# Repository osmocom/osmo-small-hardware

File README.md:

osmo-small-hardware - Various small Osmocom Hardware Projects
=============================================================

This repository contains a number of OSHW (open source hardware)
designs.  They are part of the [Osmocom](https://osmocom.org/) Open
Source Mobile Communications project.

Most of the designs are done in EAGLE CAD; the schematics and board
design files as well as the BOM are contained in this repository.

GIT Repository
--------------

You can clone from the official osmo-small-hardware repository using

	git clone https://gitea.osmocom.org/electronics/osmo-small-hardware

There is a web interface at <https://gitea.osmocom.org/electronics/osmo-small-hardware>

Contributing
------------

Our coding standards are described at
https://osmocom.org/projects/cellular-infrastructure/wiki/Coding_standards

We us a gerrit based patch submission/review process for managing
contributions.  Please see
https://osmocom.org/projects/cellular-infrastructure/wiki/Gerrit for
more details

clock-converter
---------------

The osmo-clock-conv is a small board for low-jitter conversion of a sine
clock into a square clock, based around the LTC6957-4.

* [Homapege](https://osmocom.org/projects/osmo-clock-conv)

clock-generator
---------------

Osmocom Clock Generator board, using the Si5351C clock synthesizer to
derive up to 8 different clocks from a single clock reference, such as a
10MHz GPS-DO or OCXO.

* [Homepage](https://osmocom.org/projects/osmo-clock-gen)

dus-lmt-breakout
----------------

This is a break-out board for the LMT port of Ericsson DUS-31/41
baseband units.

e1-tap
------

The Osmocom E1/T1 tap adapter allows you to tap into the communication
of an E1/T1 line.

* [Homepage](https://osmocom.org/projects/e1-tap)

eksos-rj45-breakout
-------------------

This contains a couple of break-out boards which can be used to break out the
ISDN / PSTN ports of a Nokia EKSOS V5 access network.

gtm900-breakout
---------------

Break-out board for the GTM900B Calypso based GSM cellular modem.

mpcie-breakout
--------------

This is a small break-out board for miniPCIe (mPCIe) type cellular /
WWAN modems.

* [Homepage](https://osmocom.org/projects/mpcie-breakout)

multivoltage-uart
-----------------

* [Homepage](https://osmocom.org/projects/mv-uart)

ngff-breakout
-------------

This is a small break-out board for M.2 (NGFF) type cellular / WWAN
modems.

* [Homepage](https://osmocom.org/projects/ngff-breakout)

ohm4-ocxo
---------

osmo-lea6t-gps
--------------

Small evaluation board for the u-blox LEA6-T timing GPS receiver.

osmo-nvs-gps
------------

Small evaluation board for the NVS GPS receiver.

rj45-jumper-box
---------------

A jumper box for RJ45 cables. Useful for the many different RS232
console pin-outs on RJ45.

* [Homepage](https://osmocom.org/projects/misc-hardware/wiki/RJ45_jumper_box)

rj45-switch
-----------

sc14dect-breakout
-----------------

Small evaluation board for the SC15 DECT module

sfp-breakout + sfp-experimenter
-------------------------------

Boards for playing with SFP transceivers

* [Homepage](https://osmocom.org/projects/misc-hardware/wiki/Sfp-breakout)

siu-clock-breakout
------------------

A break-out board for the clock/sync port on the Ericsson SIU-02

rbs6k-diy-rack
--------------

A DYI small rack for housing Ericsson RBS 6000 equipment like DUL + DUG + RUS made from wooden panels and a laser-cut back plate for fans.

fcd155-breakout
---------------

This is a small break-out board to adapt the RAD FCD-155 8xE1 high-density 44-pin D-SUB connector to 8xRJ45 in standard E1 pinout.

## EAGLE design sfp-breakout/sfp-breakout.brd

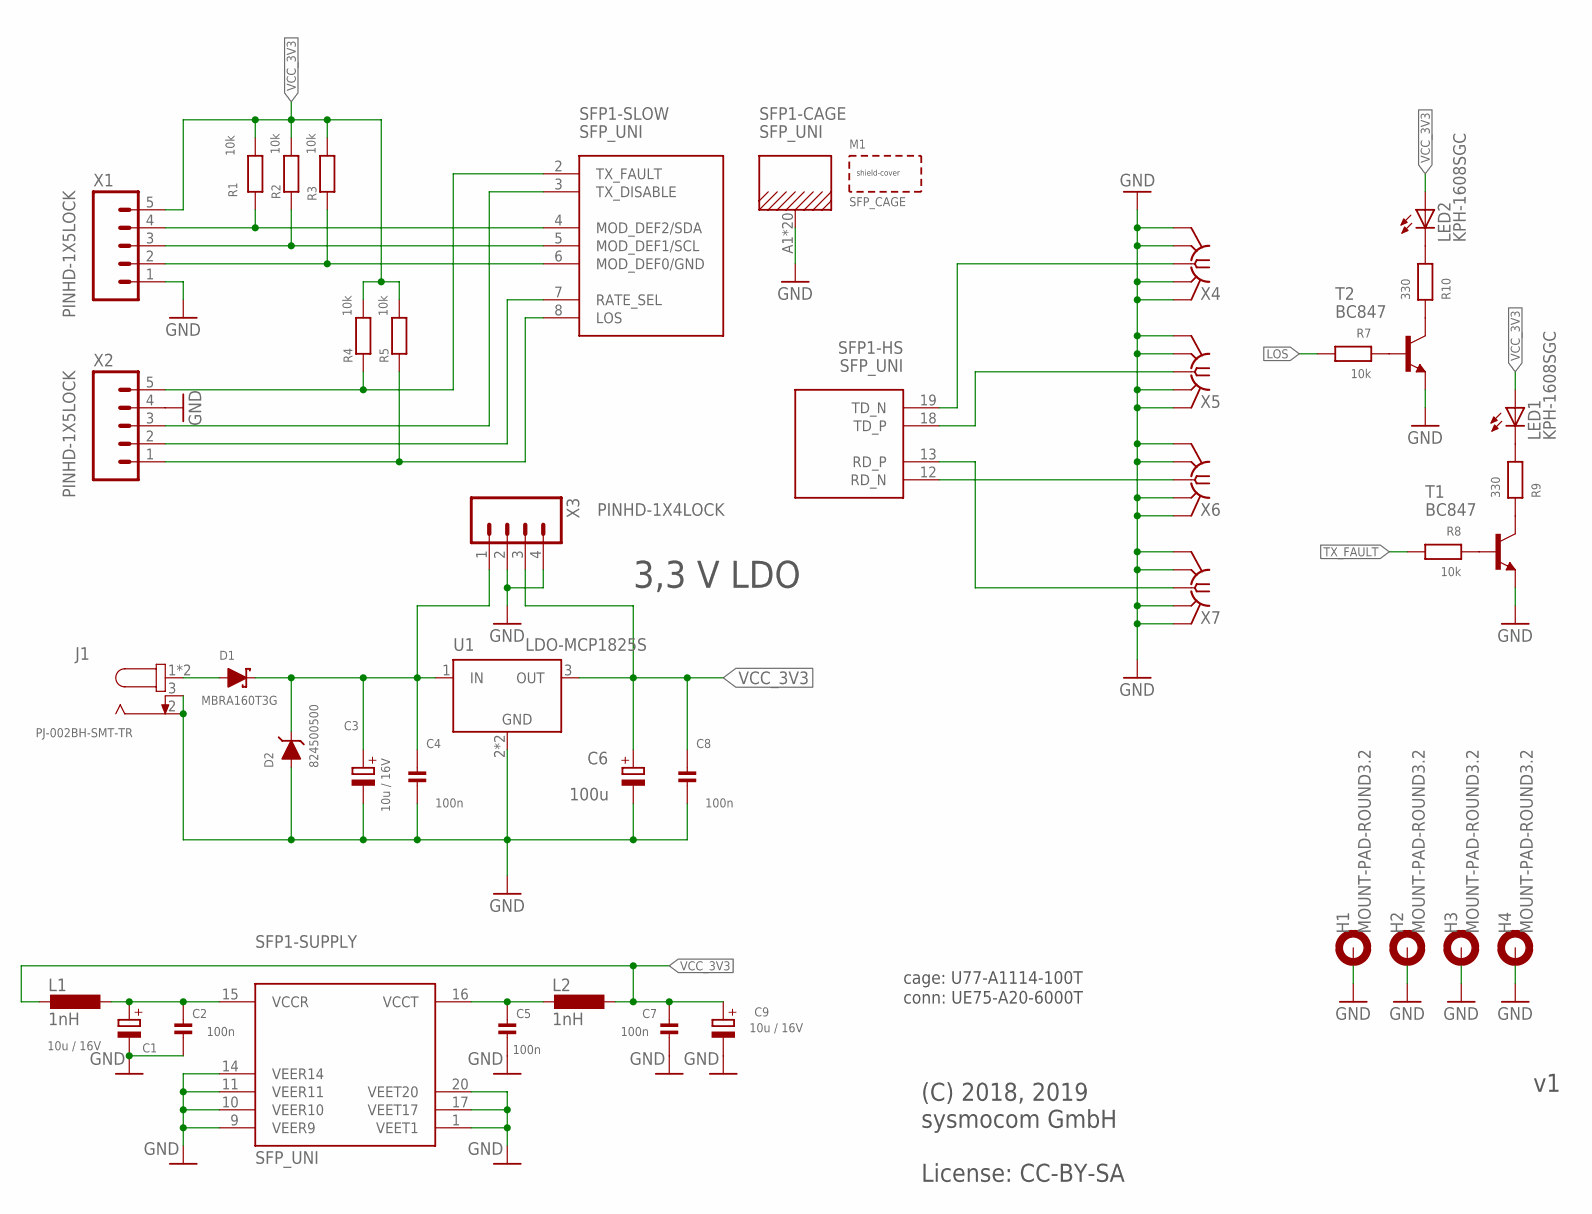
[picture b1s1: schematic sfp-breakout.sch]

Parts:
C1, C3, C9: 10u / 16V; CPOL1206; MANUFACTURERPARTNUMBER CL31A106KOHNNNE
C2, C4, C5, C7, C8: 100n; _0603; MANUFACTURERPARTNUMBER CL10B104KO8NNNC
C6: 100u; CT6032; MANUFACTURERPARTNUMBER TPSC107K006R0150
D1: MBRA160T3G; SMADIODE; MANUFACTURERPARTNUMBER B260A-13-F
D2: 824500500; SMADIODE; MANUFACTURERPARTNUMBER 824500500
H1, H2, H3, H4: MOUNT-PAD-ROUND3.2; 3,2-PAD; MANUFACTURERPARTNUMBER UNKNOWN MANUFACTURER PART NUMBER
J1: PJ-002BH-SMT-TR; 694108106102; MANUFACTURERPARTNUMBER PJ-002BH-SMT-TR
L1, L2: 1nH; 0603; MANUFACTURERPARTNUMBER AIMC-0603-1N0S-T
LED1, LED2: KPH-1608SGC; CHIP-LED0603; MANUFACTURERPARTNUMBER UNKNOWN MANUFACTURER PART NUMBER
R1, R2, R3, R4, R5, R7, R8: 10k; _0603; MANUFACTURERPARTNUMBER RMCF0603FT10K0
R9, R10: 330; _0603; MANUFACTURERPARTNUMBER RC0603FR-07330RL
SFP1: SFP_UNI; SFP_COMBINED; MANUFACTURERPARTNUMBER UE75-A20-6000T
T1, T2: BC847; SOT23-BEC; MANUFACTURERPARTNUMBER BC847C,215
U1: LDO-MCP1825S; SOT223; MANUFACTURERPARTNUMBER MCP1825ST-3302E/DB
X1, X2: PINHD-1X5LOCK; 1X05_LOCK; MANUFACTURERPARTNUMBER UNKNOWN MANUFACTURER PART NUMBER
X3: PINHD-1X4LOCK; 1X04_LOCK; MANUFACTURERPARTNUMBER UNKNOWN MANUFACTURER PART NUMBER
X4, X5, X6, X7: SMA-F-S-EDGE; MANUFACTURERPARTNUMBER UNKNOWN MANUFACTURER PART NUMBER

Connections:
+VIN: C3.+, C4.1, D1.C, D2.C, U1.1 (IN), X3.1
GND: C1.-, C2.2, C3.-, C4.2, C5.2, C6.-, C7.2, C8.2, C9.-, D2.A, H1.B3,2, H2.B3,2, H3.B3,2, H4.B3,2, J1.2, J1.3, SFP1.1 (VEET1), SFP1.9 (VEER9), SFP1.10 (VEER10), SFP1.11 (VEER11), SFP1.14 (VEER14), SFP1.17 (VEET17), SFP1.20 (VEET20), SFP1.A1 (CAGE), SFP1.A2 (CAGE), SFP1.A3 (CAGE), SFP1.A4 (CAGE), SFP1.A5 (CAGE), SFP1.A6 (CAGE), SFP1.A7 (CAGE), SFP1.A8 (CAGE), SFP1.A10 (CAGE), SFP1.A11 (CAGE), SFP1.A12 (CAGE), SFP1.B1 (CAGE), SFP1.B2 (CAGE), SFP1.B3 (CAGE), SFP1.B4 (CAGE), SFP1.B5 (CAGE), SFP1.B6 (CAGE), SFP1.B7 (CAGE), SFP1.B8 (CAGE), SFP1.B10 (CAGE), T1.E, T2.E, U1.2 (GND), U1.4 (GND), X1.1, X2.4, X3.2, X3.4, X4.BG1 (GND), X4.BG2 (GND), X4.TG1 (GND), X4.TG2 (GND), X5.BG1 (GND), X5.BG2 (GND), X5.TG1 (GND), X5.TG2 (GND), X6.BG1 (GND), X6.BG2 (GND), X6.TG1 (GND), X6.TG2 (GND), X7.BG1 (GND), X7.BG2 (GND), X7.TG1 (GND), X7.TG2 (GND)
LOS: R5.1, R7.2, SFP1.8 (LOS), X2.1
MOD_DEF0/GND: R3.1, SFP1.6 (MOD_DEF0/GND), X1.2
MOD_DEF1/SCL: R2.1, SFP1.5 (MOD_DEF1/SCL), X1.3
MOD_DEF2/SDA: R1.1, SFP1.4 (MOD_DEF2/SDA), X1.4
unnamed: D1.A, J1.1, J1.1-1 (1)
unnamed: R7.1, T2.B
unnamed: LED2.C, R10.2
unnamed: C5.1, L2.2, SFP1.16 (VCCT)
unnamed: C1.+, C2.1, L1.1, SFP1.15 (VCCR)
unnamed: R10.1, T2.C
unnamed: R8.1, T1.B
unnamed: LED1.C, R9.2
unnamed: R9.1, T1.C
RATE_SEL: SFP1.7 (RATE_SEL), X2.2
RD_N: SFP1.12 (RD_N), X6.C (1)
RD_P: SFP1.13 (RD_P), X7.C (1)
TD_N: SFP1.19 (TD_N), X4.C (1)
TD_P: SFP1.18 (TD_P), X5.C (1)
TX_DISABLE: SFP1.3 (TX_DISABLE), X2.3
TX_FAULT: R4.1, R8.2, SFP1.2 (TX_FAULT), X2.5
VCC_3V3: C6.+, C7.1, C8.1, C9.+, L1.2, L2.1, LED1.A, LED2.A, R1.2, R2.2, R3.2, R4.2, R5.2, U1.3 (OUT), X1.5, X3.3

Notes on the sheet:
3,3 V LDO
(C) 2018, 2019 sysmocom GmbH License: CC-BY-SA
cage: U77-A1114-100T
conn: UE75-A20-6000T

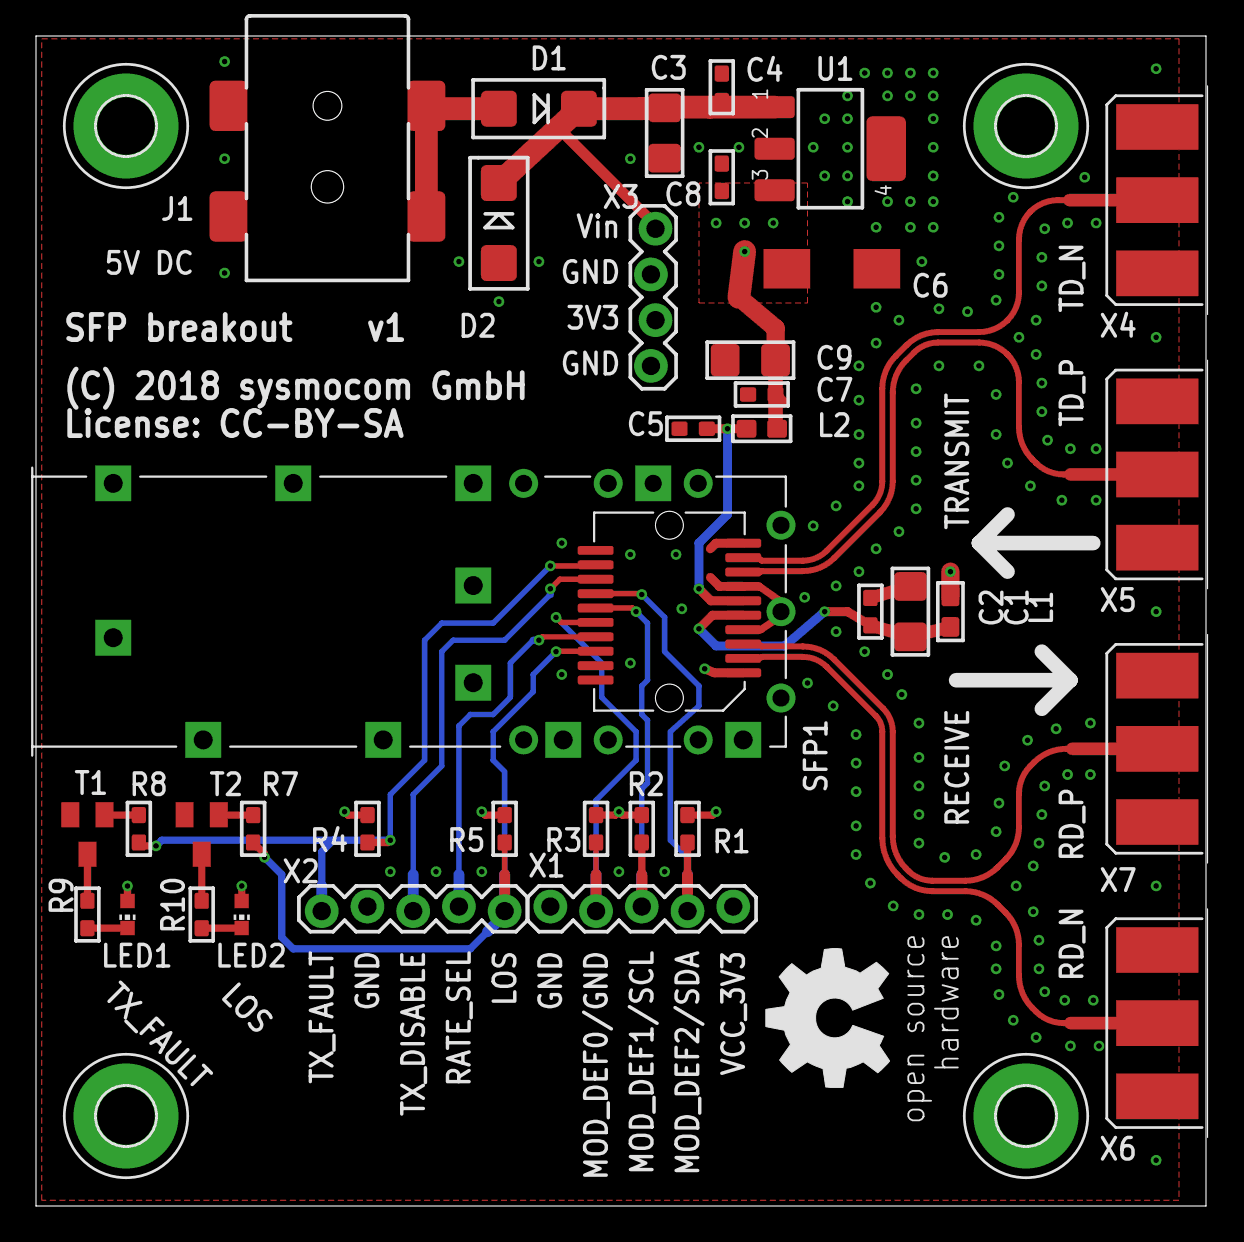
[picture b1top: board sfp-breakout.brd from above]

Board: 4 copper layers, 65.0 x 65.0 mm, 41 parts (0 on the bottom side), 23 nets.

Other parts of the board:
U$1: OSHW_8MM

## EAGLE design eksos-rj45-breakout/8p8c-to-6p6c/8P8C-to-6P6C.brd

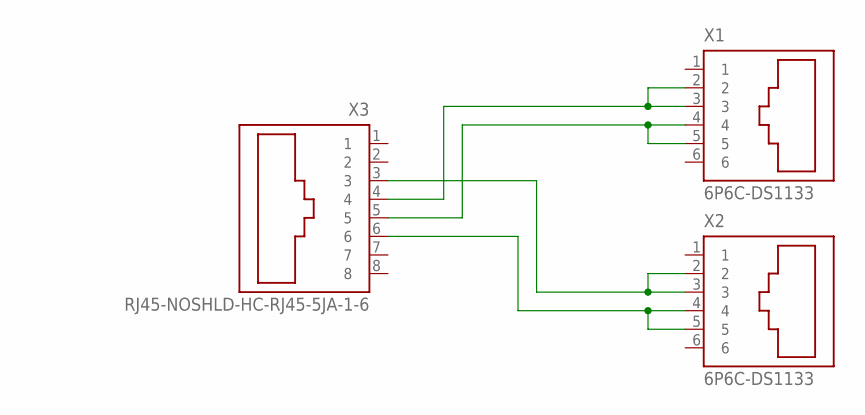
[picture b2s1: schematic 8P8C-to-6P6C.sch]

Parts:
X1, X2: 6P6C-DS1133; DS1133
X3: RJ45-NOSHLD-HC-RJ45-5JA-1-6; HC-RJ45-5JA-1-6

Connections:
unnamed: X1.2, X1.3, X3.4
unnamed: X1.4, X1.5, X3.5
unnamed: X2.2, X2.3, X3.3
unnamed: X2.4, X2.5, X3.6

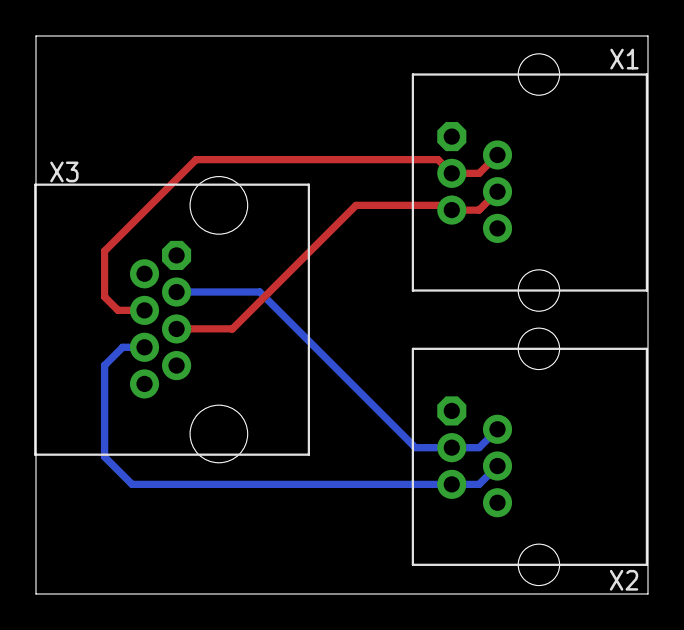
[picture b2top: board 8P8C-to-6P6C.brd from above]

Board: 2 copper layers, 34.0 x 31.0 mm, 3 parts (0 on the bottom side), 4 nets.

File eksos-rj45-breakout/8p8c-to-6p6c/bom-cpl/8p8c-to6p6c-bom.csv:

Comment,Designator,Footprint,JLCPCB Part #
6P6C,"X1, X2",DS1133,C77859
RJ45,"X3",HC-RJ45-5JA-1-6,C3000176

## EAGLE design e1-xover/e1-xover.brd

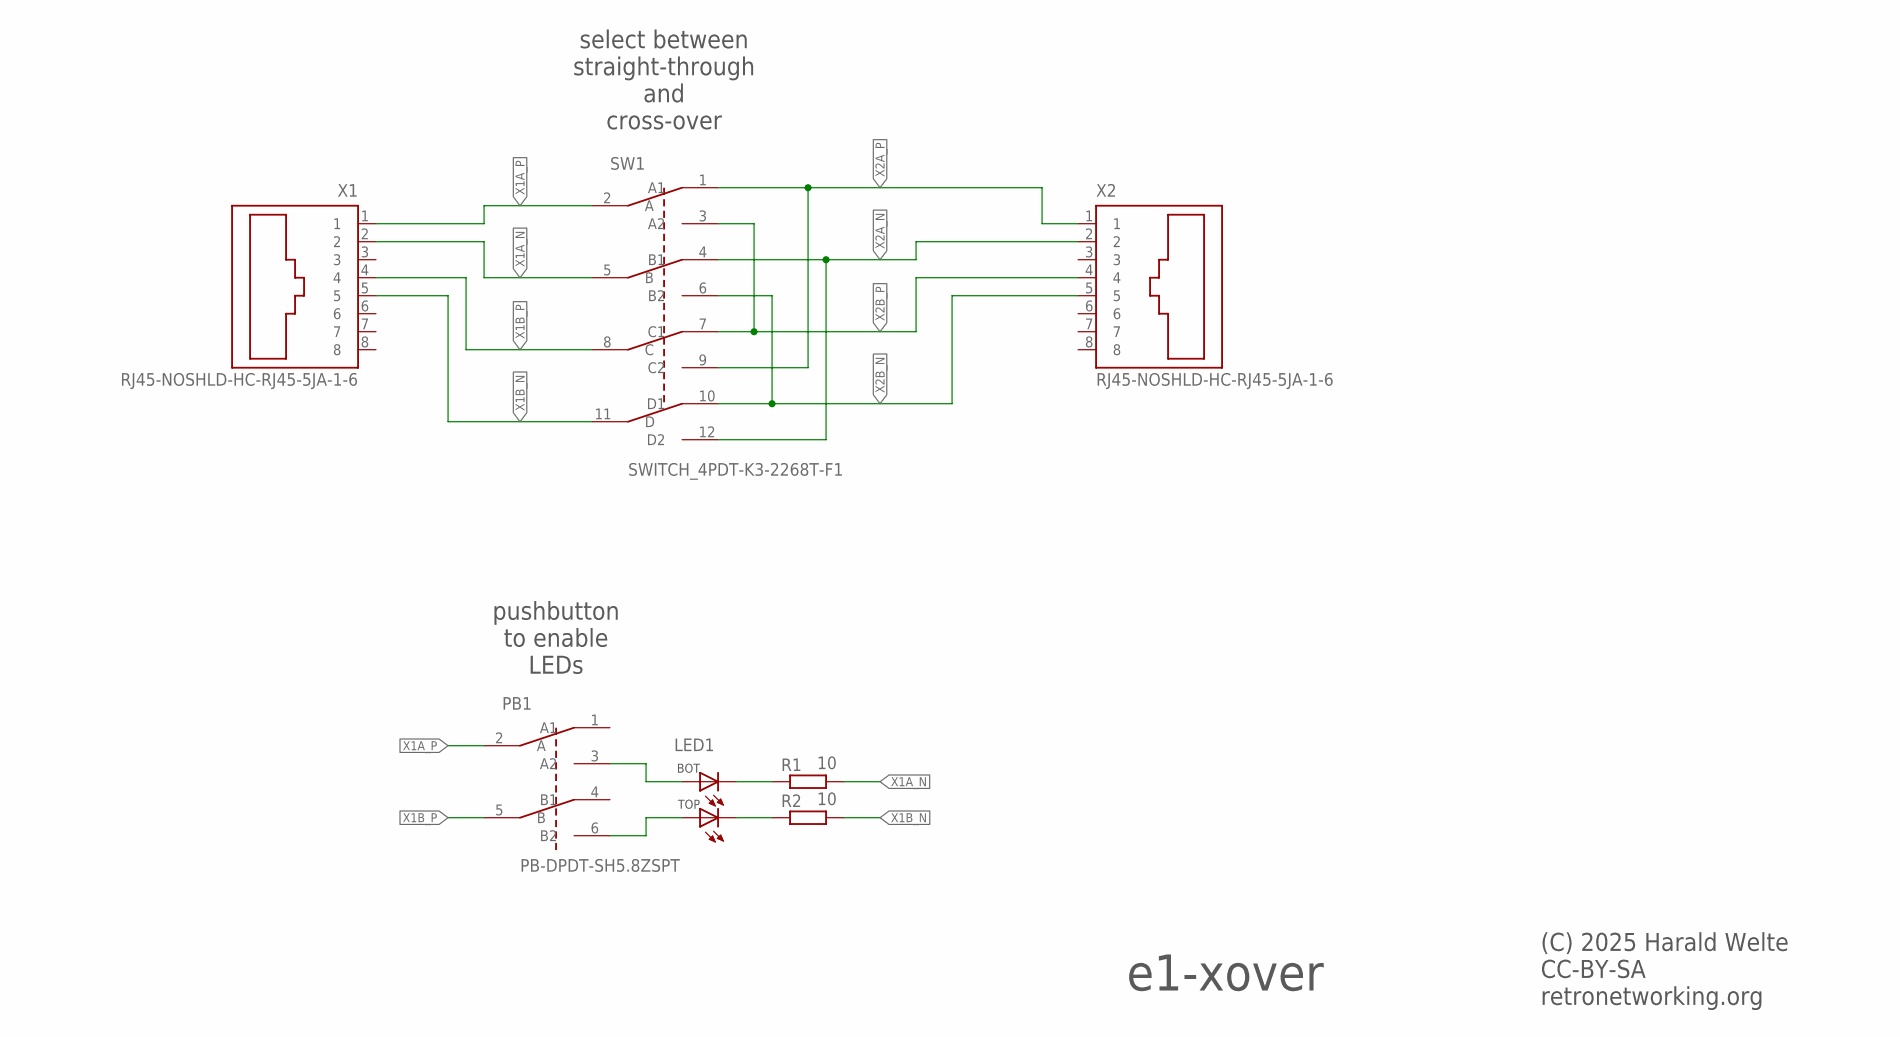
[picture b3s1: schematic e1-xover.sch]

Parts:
LED1: DIALIGHT_2V-MHK2512RGTD; MHK2512RGTD
PB1: PB-DPDT-SH5.8ZSPT; SH-5.8ZSPT
R1, R2: 10; 0207/7
SW1: SWITCH_4PDT-K3-2268T-F1; K3--2268T-F1
X1, X2: RJ45-NOSHLD-HC-RJ45-5JA-1-6; HC-RJ45-5JA-1-6

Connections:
unnamed: LED1.BK (CB), R1.1
unnamed: LED1.AK (CT), R2.1
unnamed: LED1.BA (AB), PB1.3 (A2)
unnamed: LED1.AA (AT), PB1.6 (B2)
X1A_N: R1.2, SW1.5 (B), X1.2
X1A_P: PB1.2 (A), SW1.2 (A), X1.1
X1B_N: R2.2, SW1.11 (D), X1.5
X1B_P: PB1.5 (B), SW1.8 (C), X1.4
X2A_N: SW1.4 (B1), SW1.12 (D2), X2.2
X2A_P: SW1.1 (A1), SW1.9 (C2), X2.1
X2B_N: SW1.6 (B2), SW1.10 (D1), X2.5
X2B_P: SW1.3 (A2), SW1.7 (C1), X2.4

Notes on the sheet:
e1-xover
(C) 2025 Harald Welte CC-BY-SA retronetworking.org
select between straight-through and cross-over
pushbutton to enable LEDs

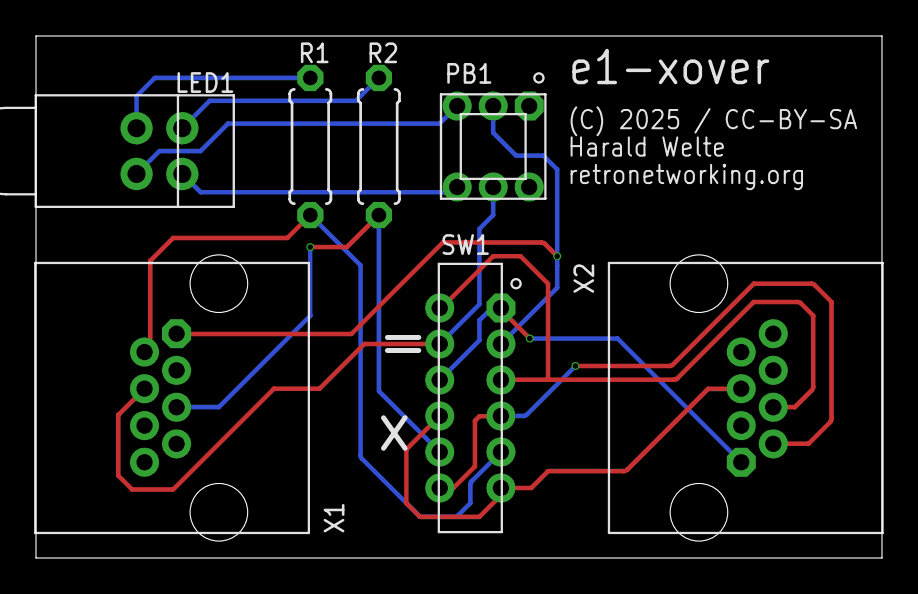
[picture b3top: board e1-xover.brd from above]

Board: 2 copper layers, 47.0 x 29.0 mm, 7 parts (0 on the bottom side), 12 nets.

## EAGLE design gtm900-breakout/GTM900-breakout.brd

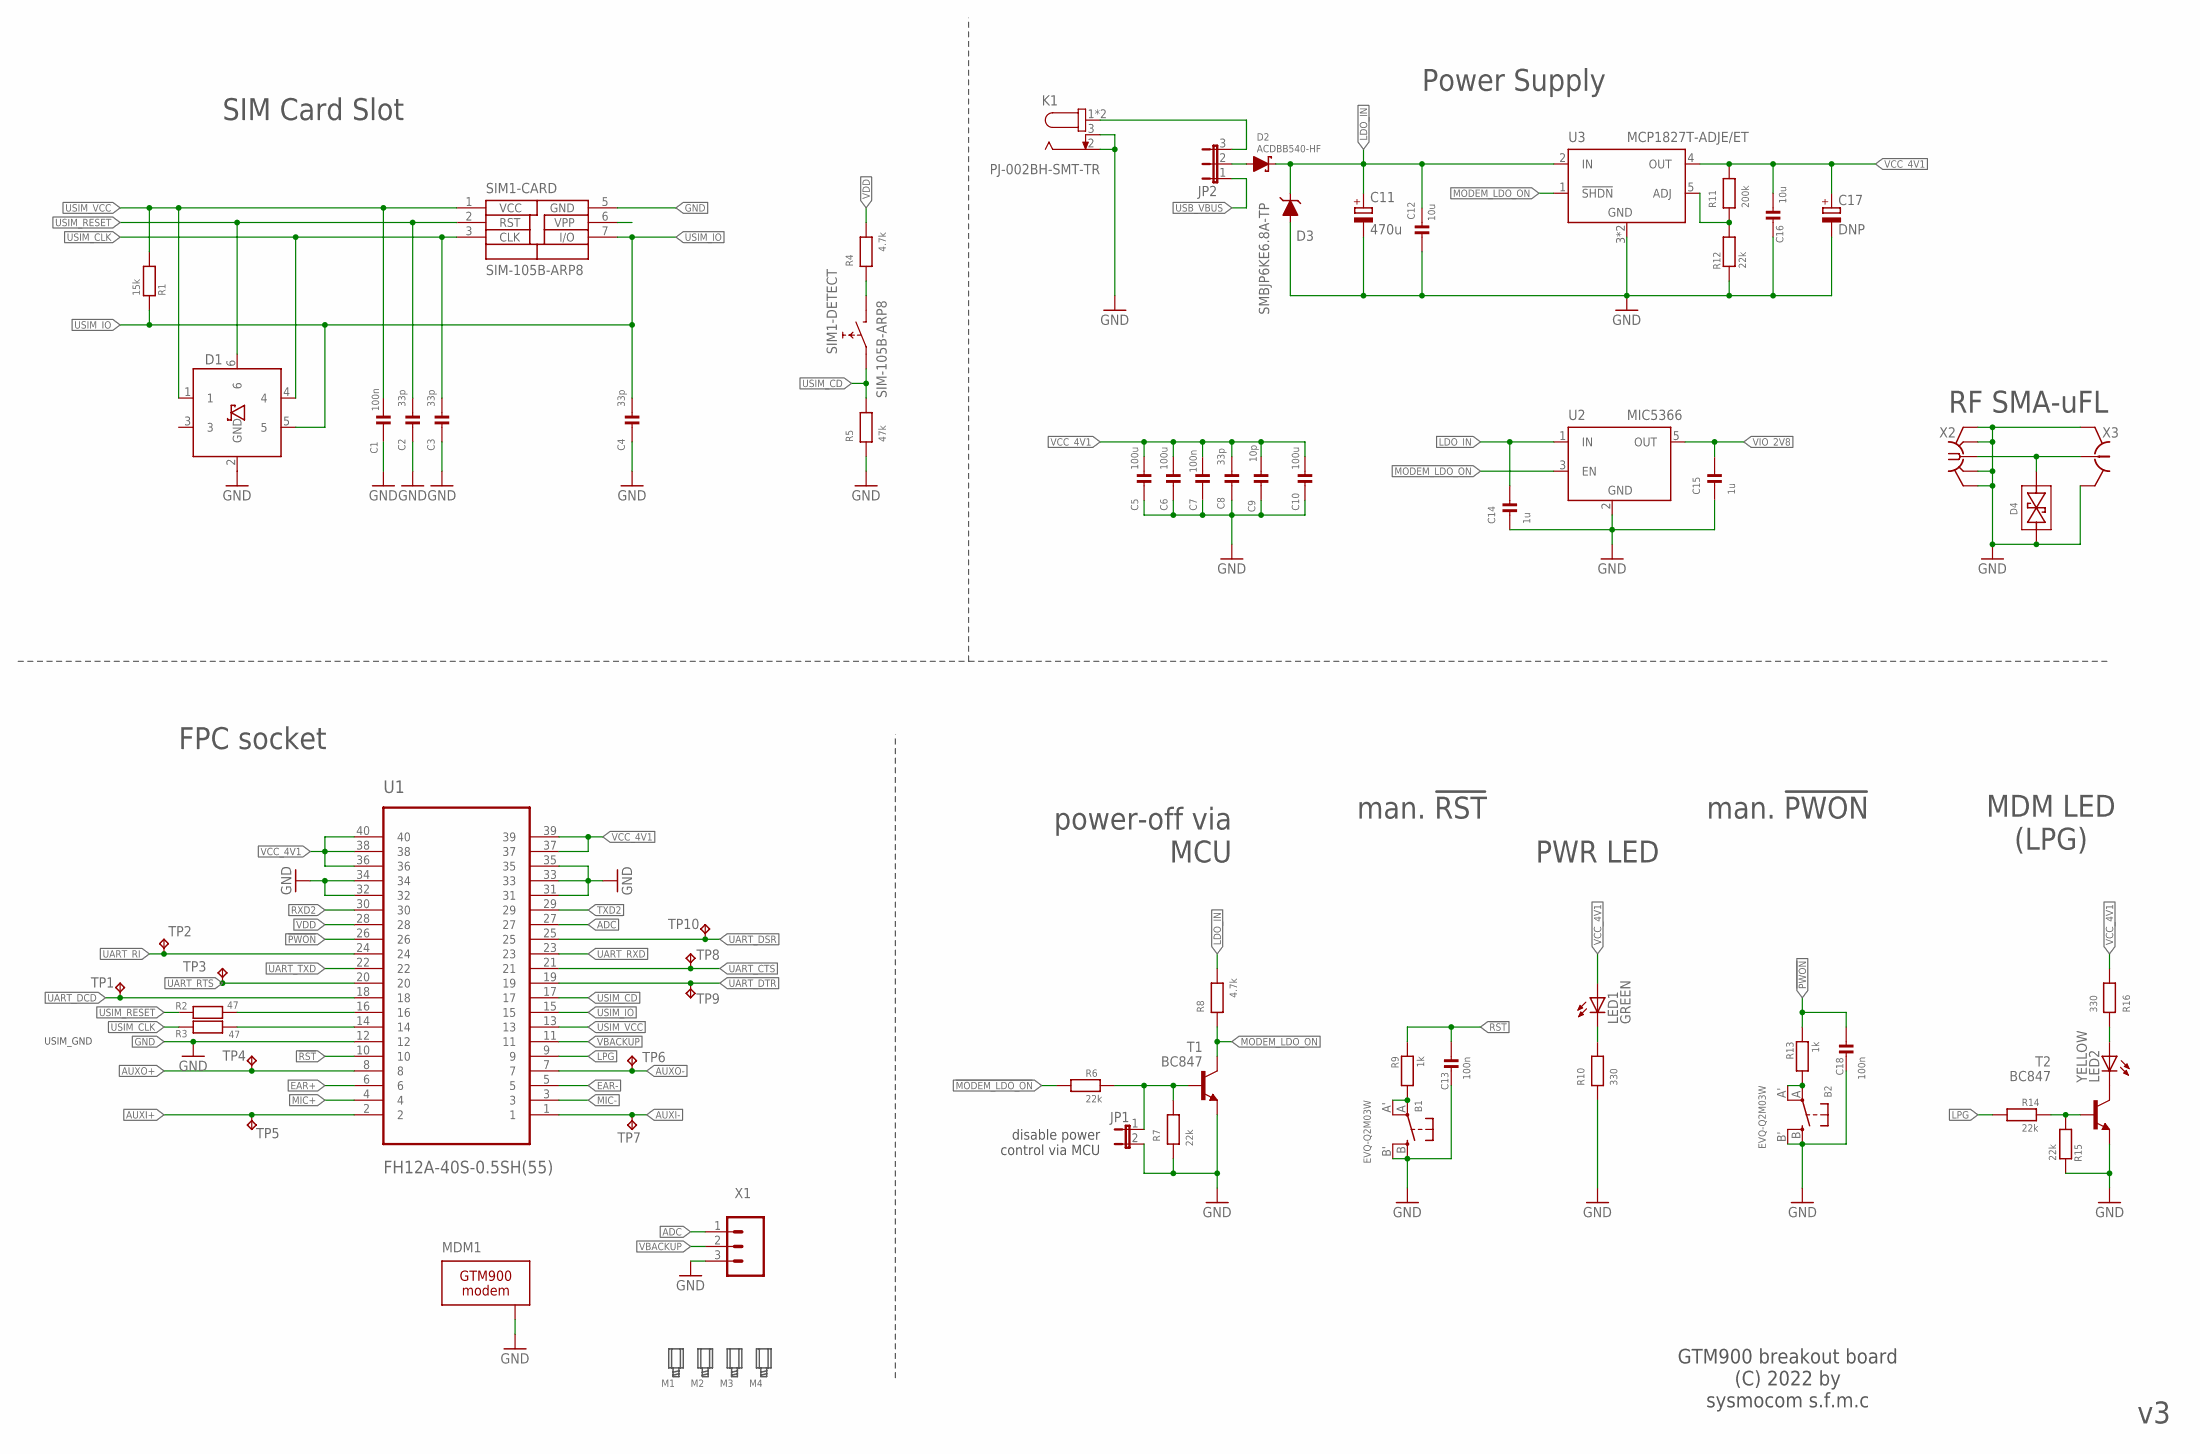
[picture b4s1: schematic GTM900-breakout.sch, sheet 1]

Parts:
B1, B2: EVQ-Q2M03W; EVQ-Q2; MANUFACTURERPARTNUMBER EVQ-Q2M03W; LCSC_PART C713484
C1, C7, C13, C18: 100n; _0603; MANUFACTURERPARTNUMBER CL10B104KB8NNWC; LCSC_PART C14663
C2, C3, C4, C8: 33p; _0402; MANUFACTURERPARTNUMBER CL05C330JB5NNNC; LCSC_PART C70465
C5, C6, C10: 100u; 1206; MANUFACTURERPARTNUMBER CL31A107MQHNNNE; LCSC_PART C15008
C9: 10p; _0603; MANUFACTURERPARTNUMBER C0603C100J5GACTU; LCSC_PART C106245
C11: 470u; UD-8X10_NICHICON; MANUFACTURERPARTNUMBER UUR0J471MNL1GS; LCSC_PART C445244
C12, C16: 10u; _0805; MANUFACTURERPARTNUMBER GRM21BR61C106KE15K; LCSC_PART C408141
C14, C15: 1u; _0603; MANUFACTURERPARTNUMBER CL10A105KO8NNNC; LCSC_PART C1592
C17: DNP; SMC_E; MANUFACTURERPARTNUMBER UNKNOWN MANUFACTURER PART NUMBER; LCSC_PART UNKNOWN LCSC_PART
D1: PESD5V0UBV; SOT666; MANUFACTURERPARTNUMBER PESD5V0U5BV,115; LCSC_PART C552582
D2: ACDBB540-HF; SMBDIODE; MANUFACTURERPARTNUMBER ACDBB540-HF; LCSC_PART C3019736
D3: SMBJP6KE6.8A-TP; SMBDIODE; MANUFACTURERPARTNUMBER SMBJP6KE6.8A-TP; LCSC_PART C725414
D4: GG040205170N2P; _0402; MANUFACTURERPARTNUMBER GG0402050R3C2P; LCSC_PART C597648
JP1: JP1E; JP1; MANUFACTURERPARTNUMBER UNKNOWN MANUFACTURER PART NUMBER; LCSC_PART UNKNOWN LCSC_PART
JP2: JP2E; JP2; MANUFACTURERPARTNUMBER UNKNOWN MANUFACTURER PART NUMBER; LCSC_PART UNKNOWN LCSC_PART
K1: PJ-002BH-SMT-TR; 694108106102; MANUFACTURERPARTNUMBER PJ-002BH-SMT-TR; LCSC_PART C3094235
LED1: GREEN; CHIP-LED0603; MANUFACTURERPARTNUMBER UNKNOWN MANUFACTURER PART NUMBER; LCSC_PART C5554150
LED2: YELLOW; CHIP-LED0603; MANUFACTURERPARTNUMBER UNKNOWN MANUFACTURER PART NUMBER; LCSC_PART C5355459
MDM1: GTM900-BM2-SPACER; GTM900-WRTHSPACER; MANUFACTURERPARTNUMBER UNKNOWN MANUFACTURER PART NUMBER; LCSC_PART UNKNOWN LCSC_PART
R1: 15k; _0603; MANUFACTURERPARTNUMBER RC0603FR-0715KL; LCSC_PART C114661
R2, R3: 47; _0603; MANUFACTURERPARTNUMBER RC0603JR-0747RL; LCSC_PART C114623
R4, R8: 4.7k; _0603; MANUFACTURERPARTNUMBER RC0603JR-074K7L; LCSC_PART C105428
R5: 47k; _0603; MANUFACTURERPARTNUMBER RC0603FR-0747KL; LCSC_PART C105579
R6, R7, R12, R14, R15: 22k; _0603; MANUFACTURERPARTNUMBER RC0603FR-0722KL; LCSC_PART C114065
R9, R13: 1k; _0603; MANUFACTURERPARTNUMBER RR0816P-102-D; LCSC_PART C116692
R10, R16: 330; _0603; MANUFACTURERPARTNUMBER RC0603JR-07330RL; LCSC_PART C105879
R11: 200k; _0603; MANUFACTURERPARTNUMBER CPF0603F200KC1; LCSC_PART C105574
SIM1: SIM-105B-ARP8; MANUFACTURERPARTNUMBER SF7W008S1AR900; LCSC_PART C920196
T1, T2: BC847; SOT23-BEC; MANUFACTURERPARTNUMBER BC847C,215; LCSC_PART C8664
TP1, TP2, TP3, TP4, TP5, TP6, TP7, TP8, TP9, TP10: TPTP10R; TP10R; MANUFACTURERPARTNUMBER UNKNOWN MANUFACTURER PART NUMBER; LCSC_PART UNKNOWN LCSC_PART
U1: FH12A-40S-0.5SH(55); HIROSE_FH12A-40S-0.5SH(55); MANUFACTURERPARTNUMBER FH12A-40S-0.5SH(55); LCSC_PART C506795
U2: MIC5366; SC70-5; MANUFACTURERPARTNUMBER MIC5366-2.8YC5-TR; LCSC_PART C626107
U3: MCP1827T-ADJE/ET; TI_KTT_DPAK2; MANUFACTURERPARTNUMBER MCP1827T-ADJE/ET; LCSC_PART C152196
X1: PINHD-1X3PTH; 1X03; MANUFACTURERPARTNUMBER UNKNOWN MANUFACTURER PART NUMBER; LCSC_PART UNKNOWN LCSC_PART
X2: SMA-F-S-TH; MANUFACTURERPARTNUMBER 5-1814832-1; LCSC_PART UNKNOWN LCSC_PART
X3: HRS_UFL; MANUFACTURERPARTNUMBER U.FL-R-SMT(01); LCSC_PART C434812

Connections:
!MODEM_LDO_ON: R6.1; also elsewhere on the board
!PWON: C18.1, R13.1, U1.26; also elsewhere on the board
!RST: C13.1, R9.1, U1.10
ADC: U1.27, X1.1
AUXI+: TP5.TP, U1.2
AUXI-: TP7.TP, U1.1
AUXO+: TP4.TP, U1.8
AUXO-: TP6.TP, U1.7
EAR+: U1.6; also elsewhere on the board
EAR-: U1.5; also elsewhere on the board
GND: B1.B (S), B1.B' (S1), B2.B (S), B2.B' (S1), C1.1, C2.2, C3.2, C4.2, C5.1, C6.1, C7.1, C8.2, C9.2, C10.1, C11.-, C12.1, C13.2, C14.1, C15.1, C16.1, C17.-, C18.2, D1.2 (GND), D3.A, D4.1, JP1.2, K1.2, K1.3, MDM1.1, MDM1.2, MDM1.3, MDM1.4, R5.1, R7.2, R10.1, R12.2, R15.2, SIM1.5 (GND), T1.E, T2.E, U1.12, U1.31, U1.32, U1.33, U1.34, U1.35, U2.2 (GND), U3.3 (GND), U3.PAD (GND), X1.3, X2.G1 (GND), X2.G2 (GND), X2.G3 (GND), X2.G4 (GND), X3.GND@1 (GND), X3.GND@2 (GND); also elsewhere on the board
LDO_IN: C11.+, C12.2, C14.2, D2.C, D3.C, R8.2, U2.1 (IN), U3.2 (IN)
LPG: R14.1, U1.9
MIC+: U1.4; also elsewhere on the board
MIC-: U1.3; also elsewhere on the board
MODEM_LDO_ON: R8.1, T1.C, U2.3 (EN), U3.1 (!SHDN)
unnamed: LED1.C, R10.2
unnamed: LED2.A, R16.2
unnamed: LED2.C, T2.C
unnamed: JP2.3, K1.1, K1.1-1 (1)
unnamed: R14.2, R15.1, T2.B
unnamed: R11.1, R12.1, U3.5 (ADJ)
unnamed: B2.A, B2.A' (P1), R13.2
unnamed: R4.1, SIM1.82 (1)
unnamed: D4.2, X2.C (1), X3.SIG (1)
unnamed: JP1.1, R6.2, R7.1, T1.B
unnamed: D2.A, JP2.2
unnamed: B1.A, B1.A' (P1), R9.2
RXD2: U1.30; also elsewhere on the board
TXD2: U1.29; also elsewhere on the board
UART_CTS: TP8.TP, U1.21; also elsewhere on the board
UART_DCD: TP1.TP, U1.18
UART_DSR: TP10.TP, U1.25
UART_DTR: TP9.TP, U1.19
UART_RI: TP2.TP, U1.24
UART_RTS: TP3.TP, U1.20; also elsewhere on the board
UART_RXD: U1.23; also elsewhere on the board
UART_TXD: U1.22; also elsewhere on the board
USB_VBUS: JP2.1; also elsewhere on the board
USIM_CD: R5.2, SIM1.81 (0), U1.17
USIM_CLK: C3.1, D1.4, R3.2, SIM1.3 (CLK)
USIM_IO: C4.1, D1.5, R1.1, SIM1.7 (I/O), U1.15
USIM_RESET: C2.1, D1.6, R2.2, SIM1.2 (RST)
USIM_VCC: C1.2, D1.1, R1.2, SIM1.1 (VCC), U1.13
USIM_VPP: SIM1.6 (VPP)
VBACKUP: U1.11, X1.2
VCC_4V1: C5.2, C6.2, C7.2, C8.1, C9.1, C10.2, C16.2, C17.+, LED1.A, R11.2, R16.1, U1.36, U1.37, U1.38, U1.39, U1.40, U3.4 (OUT)
VDD: R4.2, U1.28
VIO_2V8: C15.2, U2.5 (OUT); also elsewhere on the board
_USIM_CLK: R3.1, U1.14
_USIM_RESET: R2.1, U1.16

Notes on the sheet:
GTM900 breakout board (C) 2022 by sysmocom s.f.m.c
SIM Card Slot
FPC socket
Power Supply
RF SMA-uFL
USIM_GND
PWR LED
MDM LED (LPG)
man. !PWON
man. !RST
power-off via MCU
disable power control via MCU

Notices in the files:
amr-breakout/amr-breakout.brd:
(C) 2021 Harald Welte
CC-BY-SA 4.0
e1-xover/e1-xover.brd:
(C) 2025 / CC-BY-SA
eksos-rj45-breakout/eksos-rj45-breakout-for_slot.brd:
ISDN/POTS breakout board for Nokia EKSOS N20 (c) 2023 by Harald Welte / CC-BY-SA
gtm900-breakout/GTM900-breakout.brd:
(C) 2023 sysmocom GmbH
License: CC-BY-SA
sfp-breakout/sfp-breakout.brd:
(C) 2018 sysmocom GmbH
parts and their libraries:
Wurth_Elektronik_Electromechanic_DC_Powe: Copyright: Würth Elektronik
